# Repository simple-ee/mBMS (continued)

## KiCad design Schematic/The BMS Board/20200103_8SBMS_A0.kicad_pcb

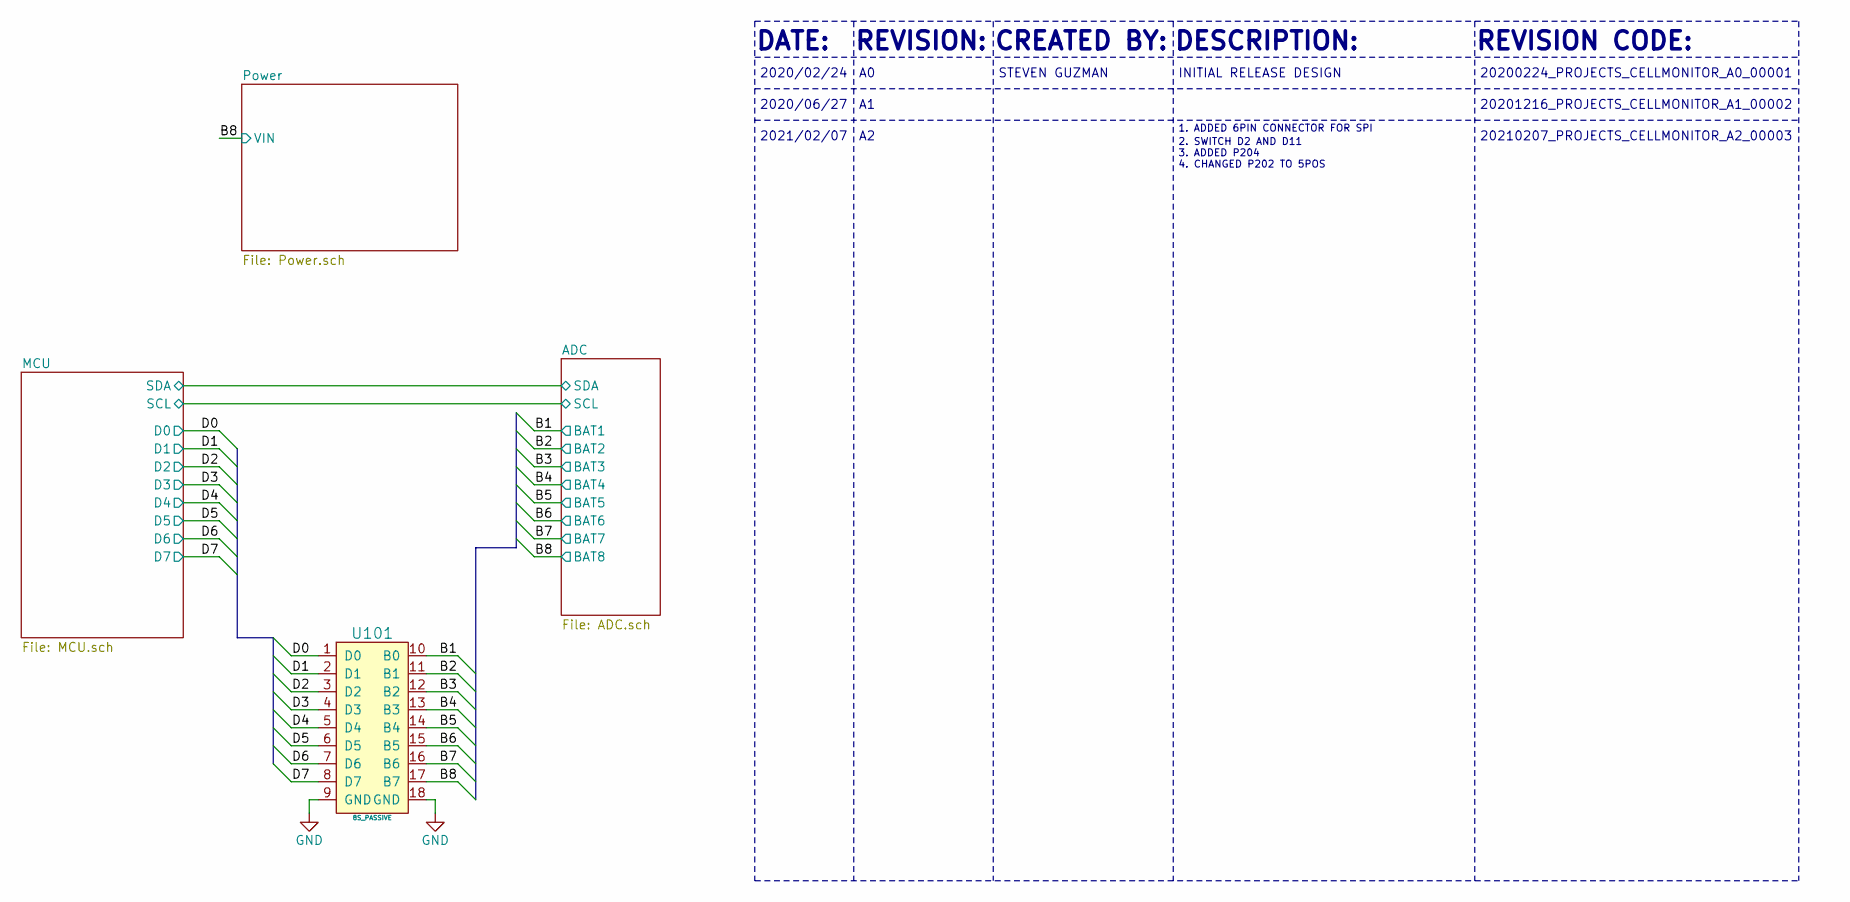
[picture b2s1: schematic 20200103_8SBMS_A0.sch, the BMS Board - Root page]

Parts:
U101: 8S_PASSIVE

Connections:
/B1: U101.10 (B0); also elsewhere on the board
/B2: U101.11 (B1); also elsewhere on the board
/B3: U101.12 (B2); also elsewhere on the board
/B4: U101.13 (B3); also elsewhere on the board
/B5: U101.14 (B4); also elsewhere on the board
/B6: U101.15 (B5); also elsewhere on the board
/B7: U101.16 (B6); also elsewhere on the board
/B8: U101.17 (B7); also elsewhere on the board
/D0: U101.1 (D0); also elsewhere on the board
/D1: U101.2 (D1); also elsewhere on the board
/D2: U101.3 (D2); also elsewhere on the board
/D3: U101.4 (D3); also elsewhere on the board
/D4: U101.5 (D4); also elsewhere on the board
/D5: U101.6 (D5); also elsewhere on the board
/D6: U101.7 (D6); also elsewhere on the board
/D7: U101.8 (D7); also elsewhere on the board
GND: U101.9 (GND), U101.18 (GND); also elsewhere on the board

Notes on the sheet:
DATE:
DESCRIPTION:
REVISION:
REVISION CODE:
2020/02/24
CREATED BY:
STEVEN GUZMAN
INITIAL RELEASE DESIGN
20200224_PROJECTS_CELLMONITOR_A0_00001
2020/06/27
20201216_PROJECTS_CELLMONITOR_A1_00002
1. ADDED 6PIN CONNECTOR FOR SPI
2021/02/07
2. SWITCH D2 AND D11 3. ADDED P204 4. CHANGED P202 TO 5POS
20210207_PROJECTS_CELLMONITOR_A2_00003

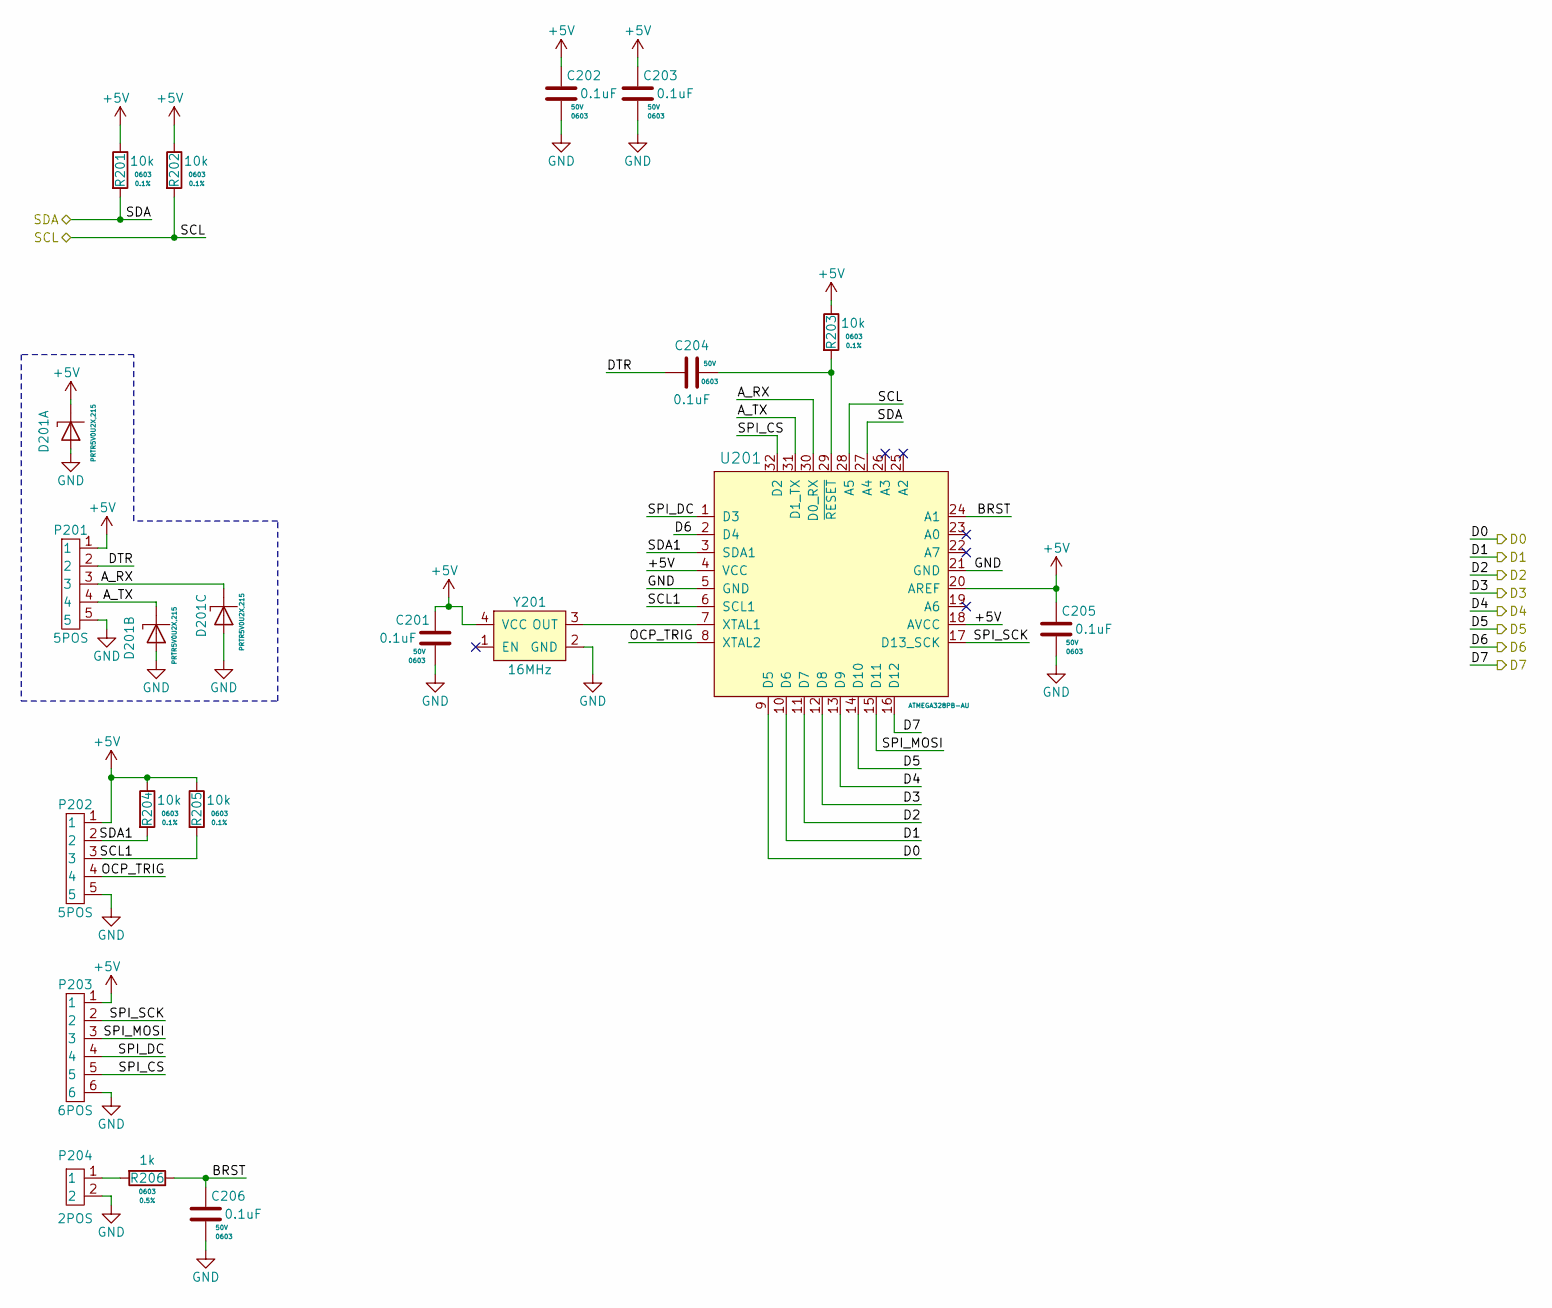
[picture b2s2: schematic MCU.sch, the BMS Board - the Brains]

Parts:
C201, C202, C203, C204, C205, C206: CL10B104KB8NNNC; C_0603_Handsolder
D201: PRTR5V0U2X,215; SOT-143
P201, P202: S5B-PH-SM4-TB(LF)(SN); S5B-PH-SM4-TB
P203: S6B-PH-SM4-TB(LF)(SN); S6B-PH-SM4-TB
P204: S2B-PH-SM4-TB(LF)(SN)
R201, R202, R203, R204, R205: ERA-3AEB103V; R_0603_Handsolder
R206: RR0816P-102-D; R_0603_Handsolder
U201: ATMEGA328PB-AU; TQFP-32
Y201: CB3-3I-16M0000; CB3

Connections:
+5V: C201.1, C202.1, C203.1, C205.1, D201.4 (K), P201.1, P202.1, P203.1, R201.1, R202.1, R203.1, R204.1, R205.1, U201.4 (VCC), U201.18 (AVCC), U201.20 (AREF), Y201.4 (VCC); also elsewhere on the board
/ADC/SCL: R202.2, U201.28 (A5); also elsewhere on the board
/ADC/SDA: R201.2, U201.27 (A4); also elsewhere on the board
/D0: U201.9 (D5); also elsewhere on the board
/D1: U201.10 (D6); also elsewhere on the board
/D2: U201.11 (D7); also elsewhere on the board
/D3: U201.12 (D8); also elsewhere on the board
/D4: U201.13 (D9); also elsewhere on the board
/D5: U201.14 (D10); also elsewhere on the board
/D6: U201.2 (D4); also elsewhere on the board
/D7: U201.16 (D12); also elsewhere on the board
/MCU/A_RX: D201.3 (K), P201.3, U201.30 (D0_RX)
/MCU/A_TX: D201.2 (K), P201.4, U201.31 (D1_TX)
/MCU/BRST: C206.1, R206.1, U201.24 (A1)
/MCU/DTR: C204.2, P201.2
/MCU/FAN1: U201.23 (A0)
/MCU/OCP_TRIG: P202.4, U201.8 (XTAL2)
/MCU/SCL1: P202.3, R205.2, U201.6 (SCL1)
/MCU/SDA1: P202.2, R204.2, U201.3 (SDA1)
/MCU/SPI_CS: P203.5, U201.32 (D2)
/MCU/SPI_DC: P203.4, U201.1 (D3)
/MCU/SPI_MOSI: P203.3, U201.15 (D11)
/MCU/SPI_SCK: P203.2, U201.17 (D13_SCK)
GND: C201.2, C202.2, C203.2, C205.2, C206.2, D201.1 (A), P201.5, P202.5, P203.6, P204.2, P204.~, U201.5 (GND), U201.21 (GND), Y201.2 (GND); also elsewhere on the board
unnamed: C204.1, R203.2, U201.29 (~RESET~)
unnamed: P204.1, R206.2
unnamed: U201.7 (XTAL1), Y201.3 (OUT)

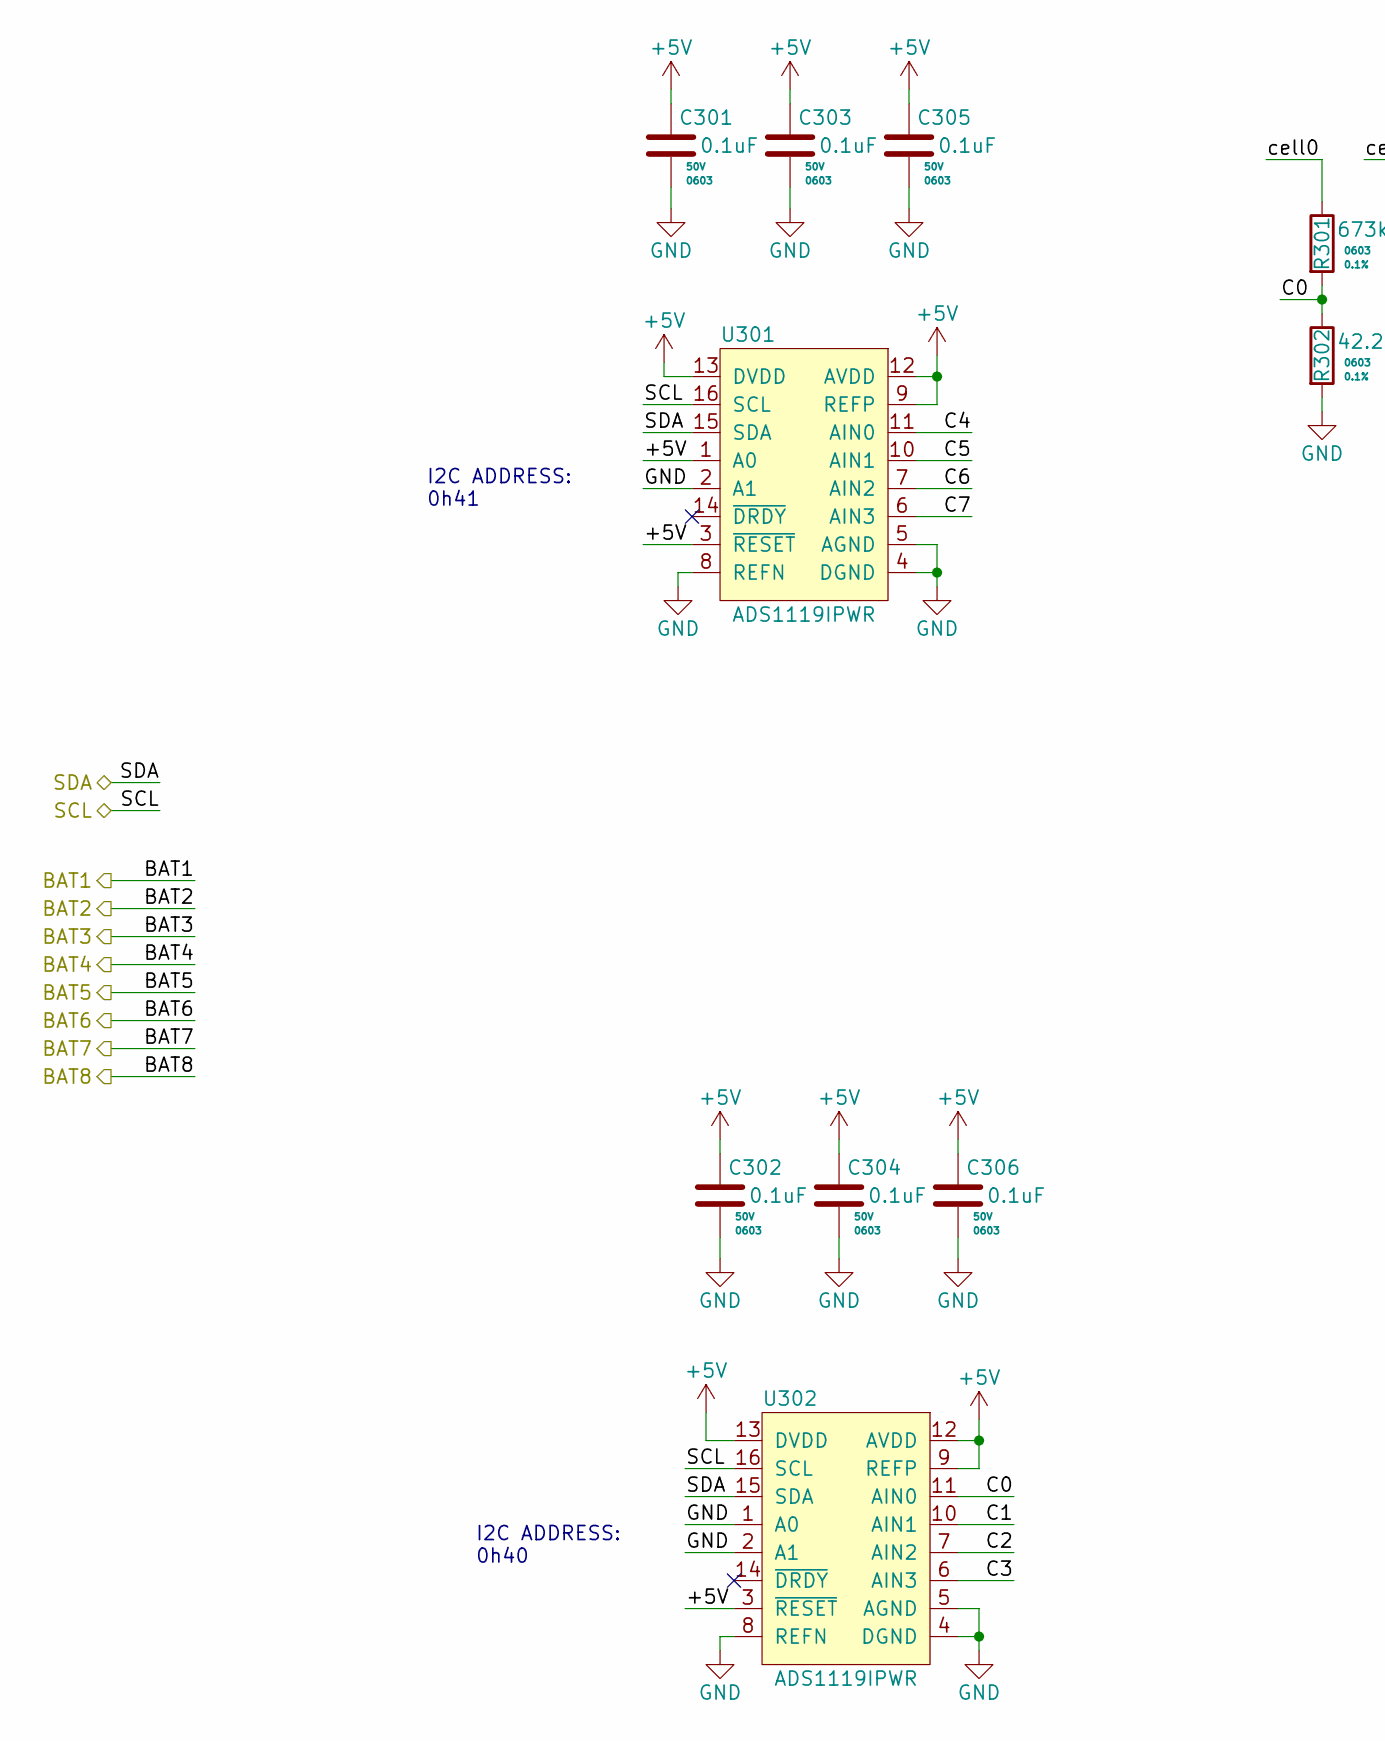
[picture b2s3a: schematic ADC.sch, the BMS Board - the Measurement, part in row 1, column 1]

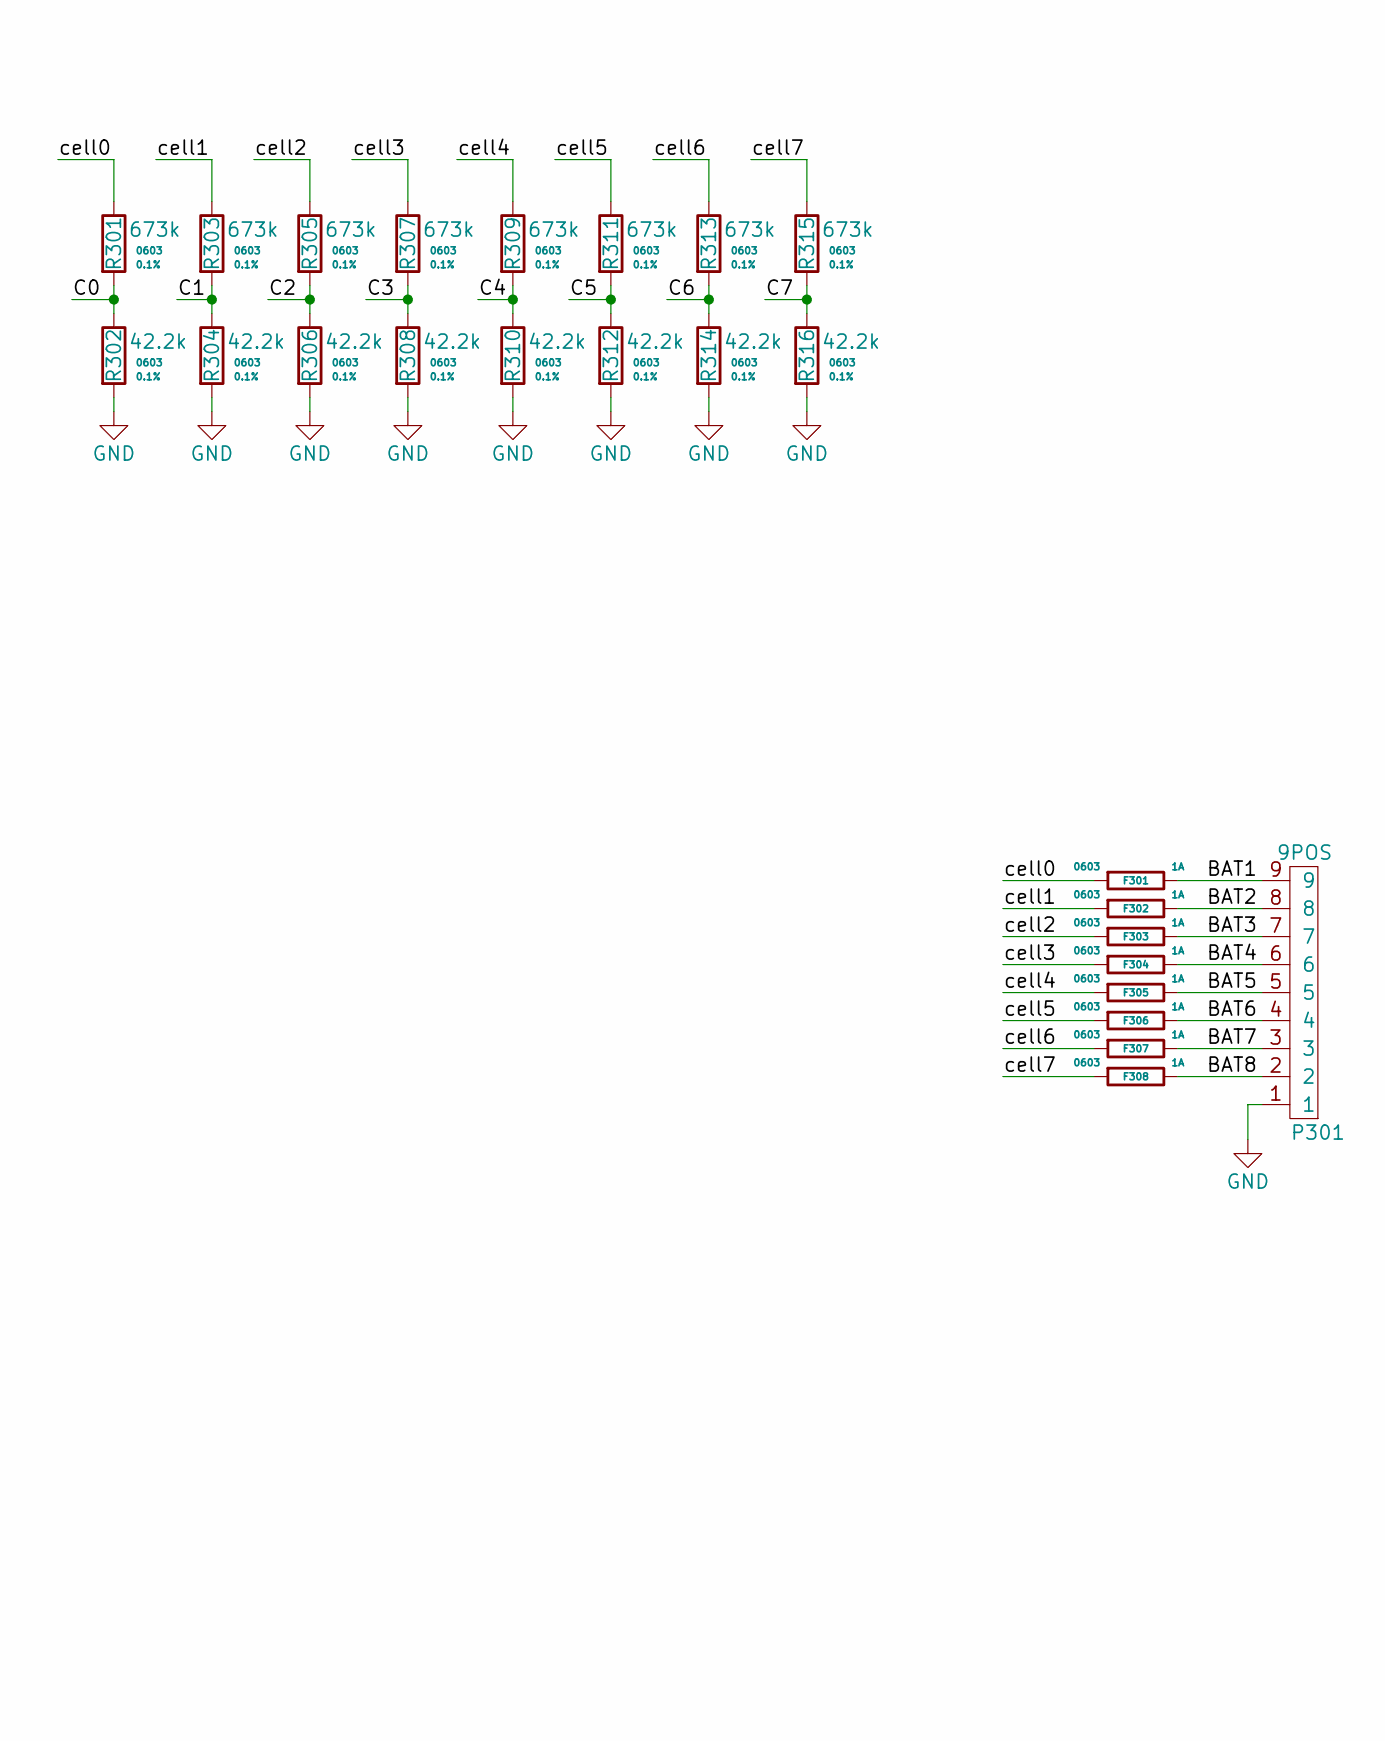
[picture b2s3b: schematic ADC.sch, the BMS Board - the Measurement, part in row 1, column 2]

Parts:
C301, C302, C303, C304, C305, C306: CL10B104KB8NNNC; C_0603_Handsolder
F301, F302, F303, F304, F305, F306, F307, F308: 0686F1000-01; Fuse_0603_1608Metric
P301: S9B-PH-SM4-TB(LF)(SN); S9B-PH-SM4-TB
R301, R303, R305, R307, R309, R311, R313, R315: RT0603BRE07673KL; R_0603_Handsolder
R302, R304, R306, R308, R310, R312, R314, R316: ERJ-PB3B4222V; R_0603_Handsolder
U301, U302: ADS1119IPWR; TSSOP-16

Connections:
+5V: C301.1, C302.1, C303.1, C304.1, C305.1, C306.1, U301.1 (A0), U301.3 (~RESET), U301.9 (REFP), U301.12 (AVDD), U301.13 (DVDD), U302.3 (~RESET), U302.9 (REFP), U302.12 (AVDD), U302.13 (DVDD); also elsewhere on the board
/ADC/C0: R301.2, R302.1, U302.11 (AIN0)
/ADC/C1: R303.2, R304.1, U302.10 (AIN1)
/ADC/C2: R305.2, R306.1, U302.7 (AIN2)
/ADC/C3: R307.2, R308.1, U302.6 (AIN3)
/ADC/C4: R309.2, R310.1, U301.11 (AIN0)
/ADC/C5: R311.2, R312.1, U301.10 (AIN1)
/ADC/C6: R313.2, R314.1, U301.7 (AIN2)
/ADC/C7: R315.2, R316.1, U301.6 (AIN3)
/ADC/SCL: U301.16 (SCL), U302.16 (SCL); also elsewhere on the board
/ADC/SDA: U301.15 (SDA), U302.15 (SDA); also elsewhere on the board
/ADC/cell0: F301.2, R301.1
/ADC/cell1: F302.2, R303.1
/ADC/cell2: F303.2, R305.1
/ADC/cell3: F304.2, R307.1
/ADC/cell4: F305.2, R309.1
/ADC/cell5: F306.2, R311.1
/ADC/cell6: F307.2, R313.1
/ADC/cell7: F308.2, R315.1
/B1: F301.1, P301.9; also elsewhere on the board
/B2: F302.1, P301.8; also elsewhere on the board
/B3: F303.1, P301.7; also elsewhere on the board
/B4: F304.1, P301.6; also elsewhere on the board
/B5: F305.1, P301.5; also elsewhere on the board
/B6: F306.1, P301.4; also elsewhere on the board
/B7: F307.1, P301.3; also elsewhere on the board
/B8: F308.1, P301.2; also elsewhere on the board
GND: C301.2, C302.2, C303.2, C304.2, C305.2, C306.2, P301.1, R302.2, R304.2, R306.2, R308.2, R310.2, R312.2, R314.2, R316.2, U301.2 (A1), U301.4 (DGND), U301.5 (AGND), U301.8 (REFN), U302.1 (A0), U302.2 (A1), U302.4 (DGND), U302.5 (AGND), U302.8 (REFN); also elsewhere on the board

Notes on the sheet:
I2C ADDRESS: 0h41
I2C ADDRESS: 0h40

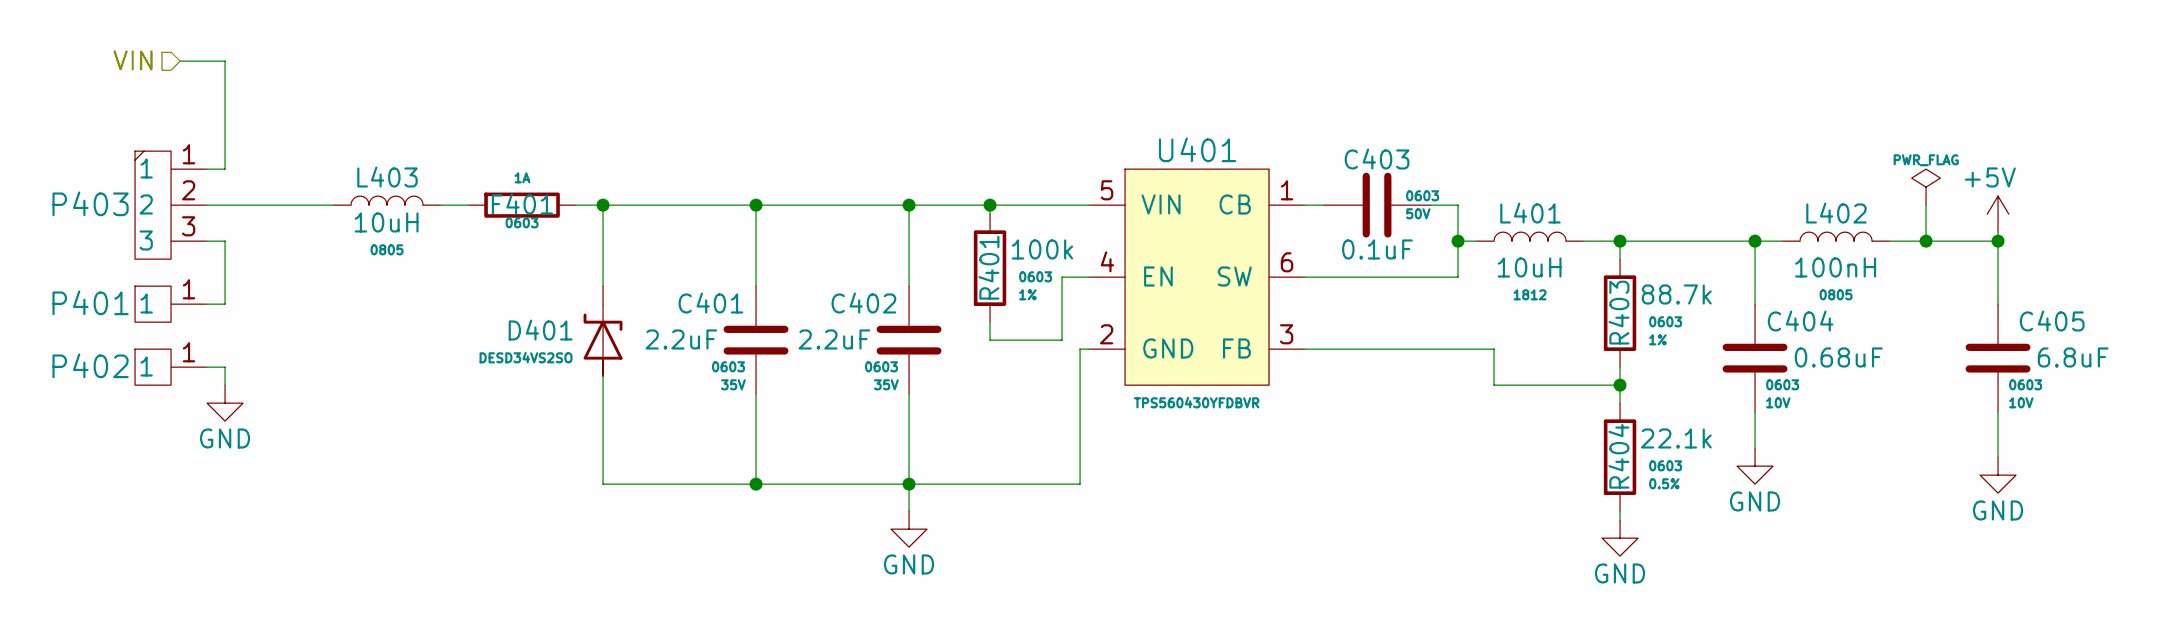
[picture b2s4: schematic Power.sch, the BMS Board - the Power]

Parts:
C401, C402: GRM188R6YA225MA12D; C_0603_Handsolder
C403: C0603C104K5RACAUTO; C_0603_Handsolder
C404: CC0603KRX7R6BB684; C_0603_Handsolder
C405: C1608X5R1A685M080AC; C_0603_Handsolder
D401: DESD34VS2SO; SOT-23-3
F401: 0686F1000-01; Fuse_0603_1608Metric
L401: LQH43PN100M26L
L402: MLZ2012DR10DT000; L_0805
L403: MLZ2012N100LT000; L_0805
P401, P402: SMD_1POS_1x2mm; SMD_1POS_1MMx2MM
P403: PH1RB-03-UA
R401: CPF0603F100KC1; R_0603_Handsolder
R403: ERJ-3EKF8872V; R_0603_Handsolder
R404: RR0816P-2212-D-34C; R_0603_Handsolder
U401: TPS560430YFDBVR; SOT-23-6

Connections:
+5V: C405.1, L402.2; also elsewhere on the board
/B8: P403.1; also elsewhere on the board
GND: C401.2, C402.2, C404.2, C405.2, D401.1 (A), D401.2 (A), P402.1, R404.2, U401.2 (GND); also elsewhere on the board
unnamed: C401.1, C402.1, D401.3 (K), F401.1, R401.1, U401.5 (VIN)
unnamed: C403.1, L401.1, U401.6 (SW)
unnamed: C403.2, U401.1 (CB)
unnamed: C404.1, L401.2, L402.1, R403.1
unnamed: F401.2, L403.2
unnamed: L403.1, P403.2
unnamed: P401.1, P403.3
unnamed: R401.2, U401.4 (EN)
unnamed: R403.2, R404.1, U401.3 (FB)

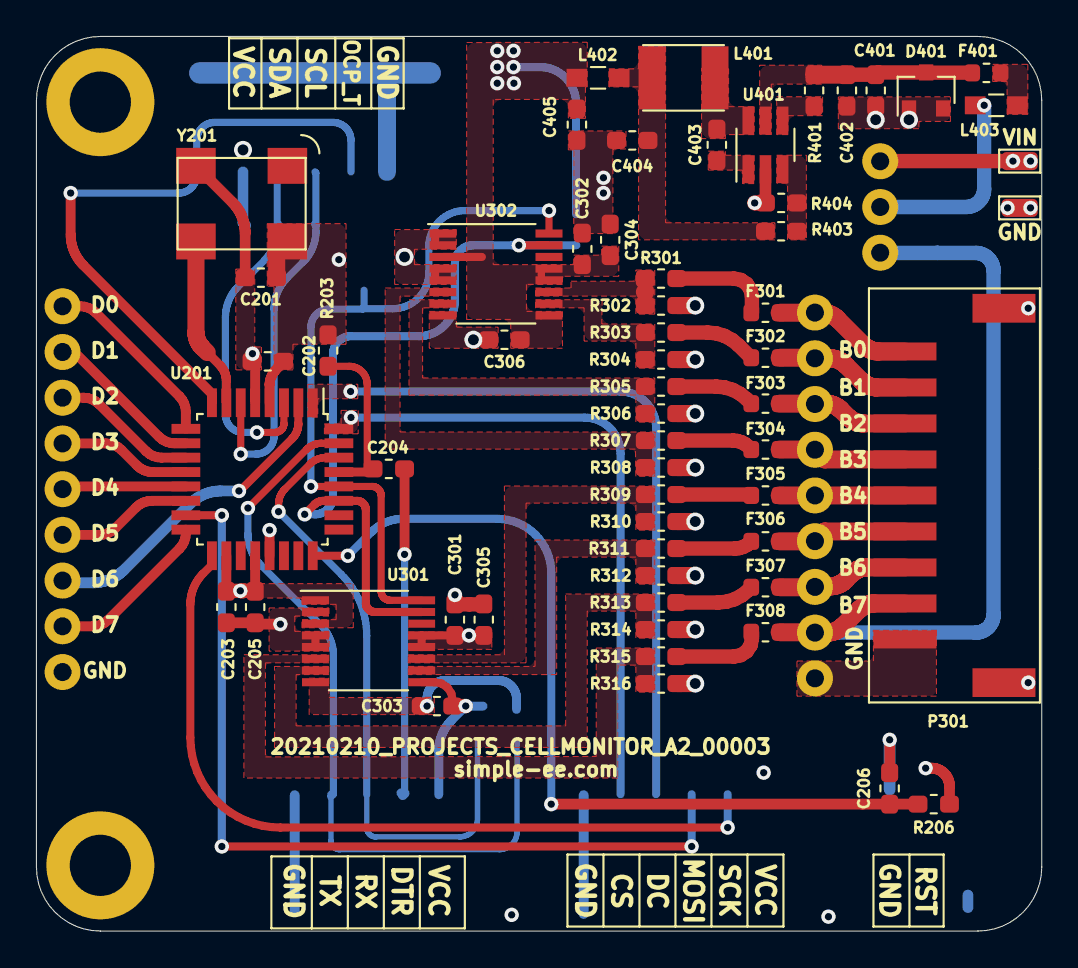
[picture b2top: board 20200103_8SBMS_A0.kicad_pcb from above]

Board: 4 copper layers, 55.9 x 49.7 mm, 70 parts (0 on the bottom side), 59 nets.

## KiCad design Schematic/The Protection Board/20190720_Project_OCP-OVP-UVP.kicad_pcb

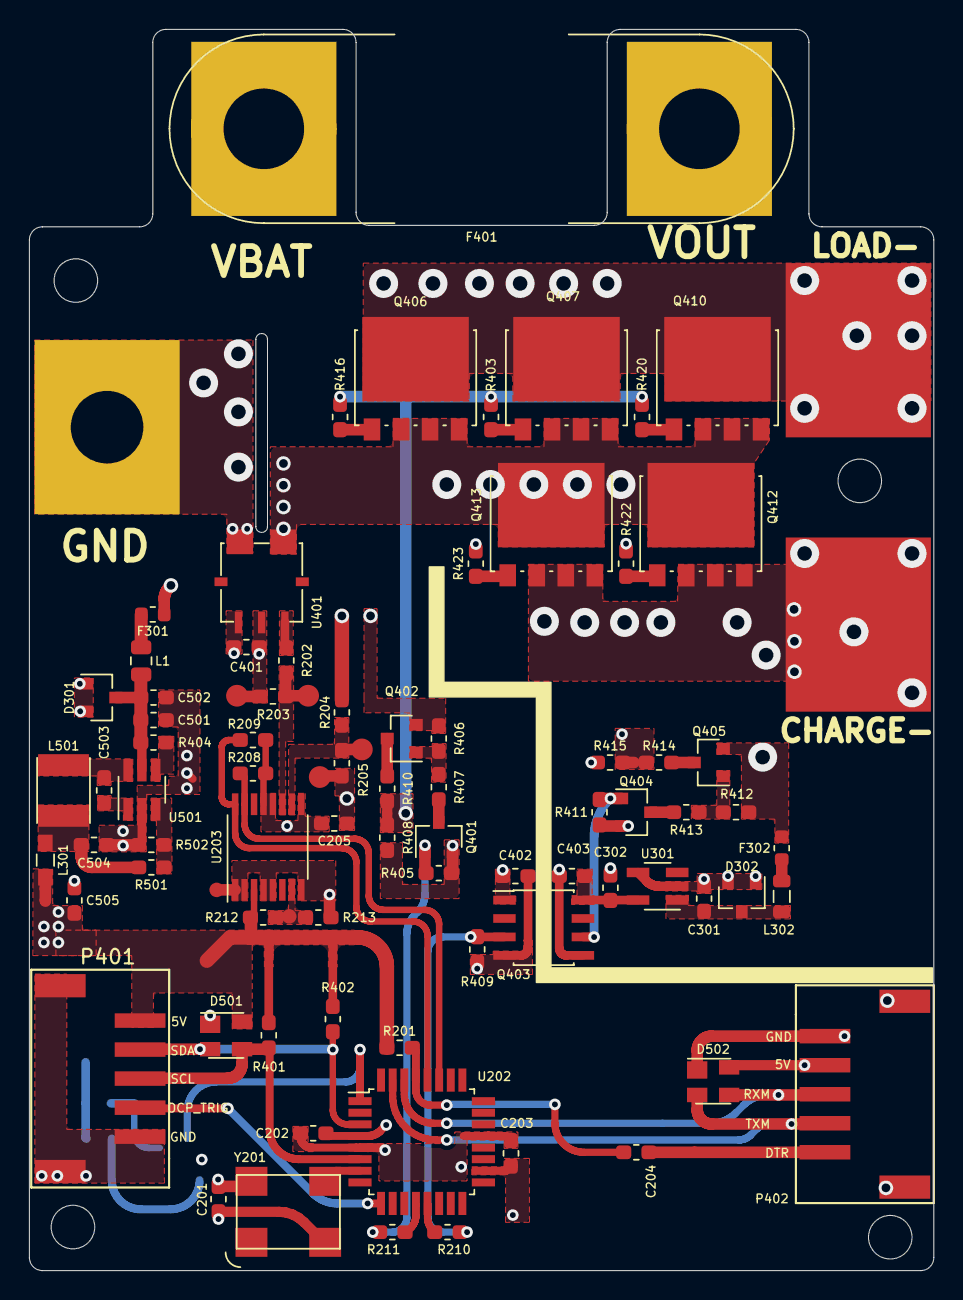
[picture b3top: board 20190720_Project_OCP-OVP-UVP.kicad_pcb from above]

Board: 4 copper layers, 62.3 x 85.5 mm, 97 parts (0 on the bottom side), 52 nets.

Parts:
C201, C202, C203, C204, C205, C206, C207, C401, C402, C403, C502, C503: C0603C104K5RACAUTO; C_0603_Handsolder
C301: GRM188R61E225KA12D; C_0603_Handsolder
C302: CL10A475MA8NQNC; C_0603_Handsolder
C501: GRM188R6YA225MA12D; C_0603_Handsolder
C504: CC0603KRX7R6BB684; C_0603_Handsolder
C505: C1608X5R1A685M080AC; C_0603_Handsolder
D301, D302: DESD34VS2SO; SOT-23-3
D501, D502: PRTR5V0U2X,215; SOT-143
F301, F302: 0686F1000-01; Fuse_0603_1608Metric
F401: 142.5631.6122; 142.5631.5702
L1, L302: MLZ2012N100LT000; L_0805_2012Metric
L301: MLZ2012DR10DT000; L_0805
L501: LQH43PN100M26L
P305, P306, P307, P308: Standoff_M3; M3X3.00MM
P401, P402: S5B-PH-SM4-TB(LF)(SN); S5B-PH-SM4-TB
P403, P404, P405: TH_1POS_10MMx12MM_M6_copy; TH_1POS_10MMx12MM_M6
P407, P408: SMD_1POS_12MM
Q401, Q404: 2N7002-7-F; SOT-23-3
Q402, Q405: BSS84LT1G; SOT-23-3
Q403: ISO7021FDR; SOIC-8
Q406, Q407, Q410, Q412, Q413: PSMNR70-40SSHJ; SOT-1235
R201, R206, R207, R208, R209, R401, R402: ERA-3AEB103V; R_0603_Handsolder
R202, R212: RC0603FR-0730KL; R_0603_Handsolder
R203, R213: RR0816P-203-D; R_0603_Handsolder
R204: RT0603BRE07673KL; R_0603_Handsolder
R205: ERJ-PB3B4222V; R_0603_Handsolder
R210, R211: RC0603FR-07470RL; R_0603_Handsolder
R403, R416, R420, R422, R423: RC0603FR-07100RL; R_0603_Handsolder
R404, R405, R406, R407, R408, R409, R410, R411, R412, R413, R414, R415: CPF0603F100KC1; R_0603_Handsolder
R501: ERJ-3EKF8872V; R_0603_Handsolder
R502: RR0816P-2212-D-34C; R_0603_Handsolder
SW201: KSC721G
TP202, TP203, TP204, TP205: TP_CIRCLE_1.5MM
TP206, TP207: TP_CIRCLE_1MM-TestPoint; TP_CIRCLE_1MM
U201: MC74HC1G04DFT1G; SOT-353_SC-70-5
U202: ATMEGA328PB-AU; TQFP-32
U203: ADS1119IPWR; TSSOP-16
U301: TPS7B6950DBVR; SOT-23-5_HandSoldering
U401: ACS781KLRTR-150B-T; PowerSMD-7
U501: TPS560430YFDBVR; SOT-23-6
Y201: CB3-3I-16M0000; CB3

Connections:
+5V: C201.2, C202.2, C203.2, C205.2, C207.2, C401.1, C402.1, C505.1, D501.4, D502.4, L301.2, P401.1, P402.4, Q403.1, R201.1, R206.1, R208.1, R209.1, R212.1, R401.1, R402.1, U201.5, U202.4, U202.18, U203.3, U203.9, U203.12, U203.13, U401.1, Y201.4
+5VD: C302.1, C403.1, Q403.8, U301.5
/MCU/CHRG_ON: Q403.3, R210.2, R409.1
/MCU/DTR: C204.2, P402.1
/MCU/GATE_LOAD: Q401.1, R211.2, R405.1
/MCU/I_OUT: R202.1, U401.3
/MCU/I_SENSE_P: R202.2, R203.1, TP202.1, U203.11
/MCU/OCP_TRIG: P401.4, U202.9
/MCU/RESTORE: U201.4, U202.1
/MCU/RX_M: D502.3, P402.3, U202.30
/MCU/SCL: R209.2, U202.28, U203.16
/MCU/SCL1: D501.3, P401.3, R401.2, U202.6
/MCU/SDA: R208.2, U202.27, U203.15
/MCU/SDA1: D501.2, P401.2, R402.2, U202.3
/MCU/TX_M: D502.2, P402.2, U202.31
/MCU/V_RAIL: R212.2, R213.1, TP206.1, U203.7
/MCU/V_SENSE_P: R204.2, R205.1, TP204.1, U203.10
/PowerFets/GC: R414.2, R415.1, R422.2, R423.1
/PowerFets/GL: R403.2, R408.1, R410.2, R416.2, R420.2
/VIN: F301.2, F401.2, P403.1, Q402.2, R204.1, R406.1
/VOUT: F302.2, F401.1, P405.1, Q405.2, R412.1
GND: C201.1, C202.1, C203.1, C205.1, C206.1, C207.1, C401.2, C402.2, C501.2, C502.1, C504.2, C505.2, D301.1, D301.2, D501.1, D502.1, P401.5, P402.5, P404.1, Q401.2, Q403.4, R203.2, R205.2, R213.2, R405.2, R408.2, R409.2, R502.2, SW201.1, TP203.1, TP205.1, TP207.1, U201.3, U202.5, U202.21, U203.1, U203.2, U203.4, U203.5, U203.8, U401.2, U401.6, U501.2, Y201.2
GNDPWR: C301.2, C302.2, C403.2, D302.1, D302.2, P408.1, Q403.5, Q404.2, Q412.2, Q412.3, Q412.4, Q413.2, Q413.3, Q413.4, R411.2, R415.2, U301.2, U301.4
unnamed: C204.1, R201.2, U202.29
unnamed: C206.2, R207.1, U201.2
unnamed: C301.1, D302.3, L302.2, U301.1
unnamed: C501.1, C502.2, D301.3, L1.2, R404.1, U501.5
unnamed: C503.1, L501.1, U501.6
unnamed: C503.2, U501.1
unnamed: C504.1, L301.1, L501.2, R501.1
unnamed: F301.1, L1.1
unnamed: F302.1, L302.1
unnamed: P407.1, Q406.5, Q407.5, Q410.5
unnamed: Q401.3, R407.2
unnamed: Q402.1, R406.2, R407.1
unnamed: Q402.3, R410.1
unnamed: Q403.6, Q404.1, R411.1
unnamed: Q404.3, R413.2
unnamed: Q405.1, R412.2, R413.1
unnamed: Q405.3, R414.1
unnamed: Q406.1, R416.1
unnamed: Q406.2, Q406.3, Q406.4, Q407.2, Q407.3, Q407.4, Q410.2, Q410.3, Q410.4, Q412.5, Q413.5, U401.5
unnamed: Q407.1, R403.1
unnamed: Q410.1, R420.1
unnamed: Q412.1, R422.1
unnamed: Q413.1, R423.2
unnamed: R206.2, R207.2, SW201.2
unnamed: R210.1, U202.13
unnamed: R211.1, U202.12
unnamed: R404.2, U501.4
unnamed: R501.2, R502.1, U501.3
unnamed: U202.7, Y201.3

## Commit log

2021-07-01 Create README.md
    Added README
2021-07-01 Update README.md
    Updated readme file
2021-07-03 Adding the Protection Board schematic files
2021-07-03 Adding gerber files
2021-07-03 Adding the BMS board kicad files
2021-07-03 Added the Passive Balance Board
2021-07-03 Added source code for the BMS Board
2021-07-07 Added images
2021-10-17 Adding wiring diagram for single 8S pack system
    Here we have a wiring diagram for a single 8S pack that will be charged by solar or external psu. Also shows the connection for providing power to an inverted or a dc load.
2021-10-17 added block diagram
2022-10-10 Updated firmware for mBMS main board
    Version A6.3 adds some tft on screen features like SoC which is actually runtime in minutes at the moment but could be changed to actual percentage
2022-10-10 Updated Protection Board code
    Added basic coulomb counter and full charge pack voltage recalibration for the counter. When the pack has his the full pack voltage value set in the parameter then the Ah of the pack will reset to en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
2023-01-13 Updated multi battery diagram
    Updated multi parallel battery diagram. Ideal diodes were incorrectly represented in position
